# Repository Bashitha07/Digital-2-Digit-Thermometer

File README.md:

# 2-Digit Digital Thermometer

A low-cost, analog **2-digit digital thermometer** designed to measure temperatures from **0 °C to 99 °C**. This project was developed for the **IE2044 – System Modelling and Prototyping** module using an LM35 temperature sensor, a TC7107 ADC/display driver, and dual seven-segment displays.

## 📌 Project Overview

The thermometer converts the LM35 sensor output directly into a temperature reading without using a microcontroller or firmware. Since the LM35 produces **10 mV/°C**, the circuit is calibrated so that each degree Celsius corresponds to one displayed count.

The design combines:

- An **LM35 precision temperature sensor**
- A **TC7107 / ICL7107 analog-to-digital converter and display driver**
- Two **common-cathode seven-segment displays**
- A calibrated **100 mV reference voltage**
- Analog star-point grounding to reduce display jitter and noise
- Visual indication for temperature overflow and underflow conditions

## ✨ Key Features

- **Measurement range:** 0 °C to 99 ��C
- **Direct voltage scaling:** 10 mV from the LM35 represents 1 °C
- **Reference calibration:** 100 mV using a 1 kΩ trimmer potentiometer
- **No microcontroller required:** Fully analog measurement and display chain
- **Overflow indication:** Red LED for temperatures above 99 °C
- **Underflow indication:** Green LED for temperatures below 0 °C
- **Noise reduction:** Analog star-point grounding using `ADND*`
- **Dual-supply operation:** +5 V and −5 V rails
- **PCB design:** Single-layer routing with SMD 0805 components

## 🧠 Operating Principle

The LM35 generates an output voltage proportional to the measured temperature:

```text
VLM35 = 10 mV × Temperature (°C)
```

For example:

```text
25 °C → 250 mV
75 °C → 750 mV
```

The TC7107 measures this analog voltage and drives the two seven-segment displays. With the reference voltage calibrated to **100 mV**, the displayed value corresponds directly to the temperature in degrees Celsius.

## 🛠️ Component Summary

| Reference | Component | Package / Type | Purpose |
|:--:|---|---|---|
| U1 | TC7107 / ICL7107 | DIP-40 | Analog-to-digital conversion and display driving |
| U2 | LM35 | TO-92, through-hole | Precision Celsius temperature sensing |
| DIS1, DIS2 | Seven-segment displays | Common cathode | Tens and units temperature display |
| RV1 | Trimmer potentiometer, 1 kΩ | Through-hole | Reference voltage adjustment |
| R1–R6 | Resistors | SMD 0805 | Input conditioning, scaling, integration, oscillator, and LED current limiting |
| C1–C4 | Capacitors | SMD 0805 | Integrator, auto-zero, reference, and oscillator timing |

## 📁 Repository Contents

```text
Digital-2-Digit-Thermometer-/
├── Diagrams/               # System block diagrams and architecture diagrams
├── Report/                 # Final project report
├── Schematics/             # Proteus simulation files and EasyEDA PCB sources
├── SMP final project.pdf   # Official module project brief and specifications
└── README.md               # Project documentation
```

## 🧪 Simulation and PCB Implementation

### Phase I — Simulation

The circuit was tested in **Proteus Design Suite 8.06** across the complete 0 °C to 99 °C operating range. The simulation also validates:

- Normal temperature measurements
- Overflow conditions above 99 °C
- Underflow conditions below 0 °C
- Seven-segment display operation
- LED error indication
- Reference-voltage calibration

### Phase II — PCB Design

The PCB was developed using **EasyEDA Pro** with the following design requirements:

- Single-layer routing
- SMD 0805 resistor and capacitor footprints
- Analog star-point grounding
- Reduced digital switching noise
- Horizontally aligned seven-segment displays
- Layout suitable for practical assembly and testing

## 🔌 Power Requirements

The design uses a dual-supply configuration:

| Supply Rail | Main Purpose |
|---|---|
| `+5 V` | Logic, display-driving, and indicator circuitry |
| `−5 V` | Analog signal processing and internal integrator operation |

> **Safety note:** Verify the power-supply polarity and voltage levels before connecting the circuit. Incorrect supply connections may damage the TC7107, LM35, displays, or other components.

## 👥 Project Team

**Module:** IE2044 – System Modelling and Prototyping  
**Academic Year:** Year 2, Semester 2  
**Institution:** Sri Lanka Institute of Information Technology (SLIIT)  
**Group:** 05

| Student | Student ID |
|---|---|
| Sellapperuma B.A. | IT24103485 |
| Jayasinghe L.P. | IT24100888 |

## 📚 Technologies and Tools

- **Proteus Design Suite 8.06** — Circuit simulation
- **EasyEDA Pro** — Schematic capture and PCB design
- **LM35** — Analog temperature sensing
- **TC7107 / ICL7107** — ADC and seven-segment display driving

## 📄 License

This project was created for academic and educational purposes as part of the IE2044 module.

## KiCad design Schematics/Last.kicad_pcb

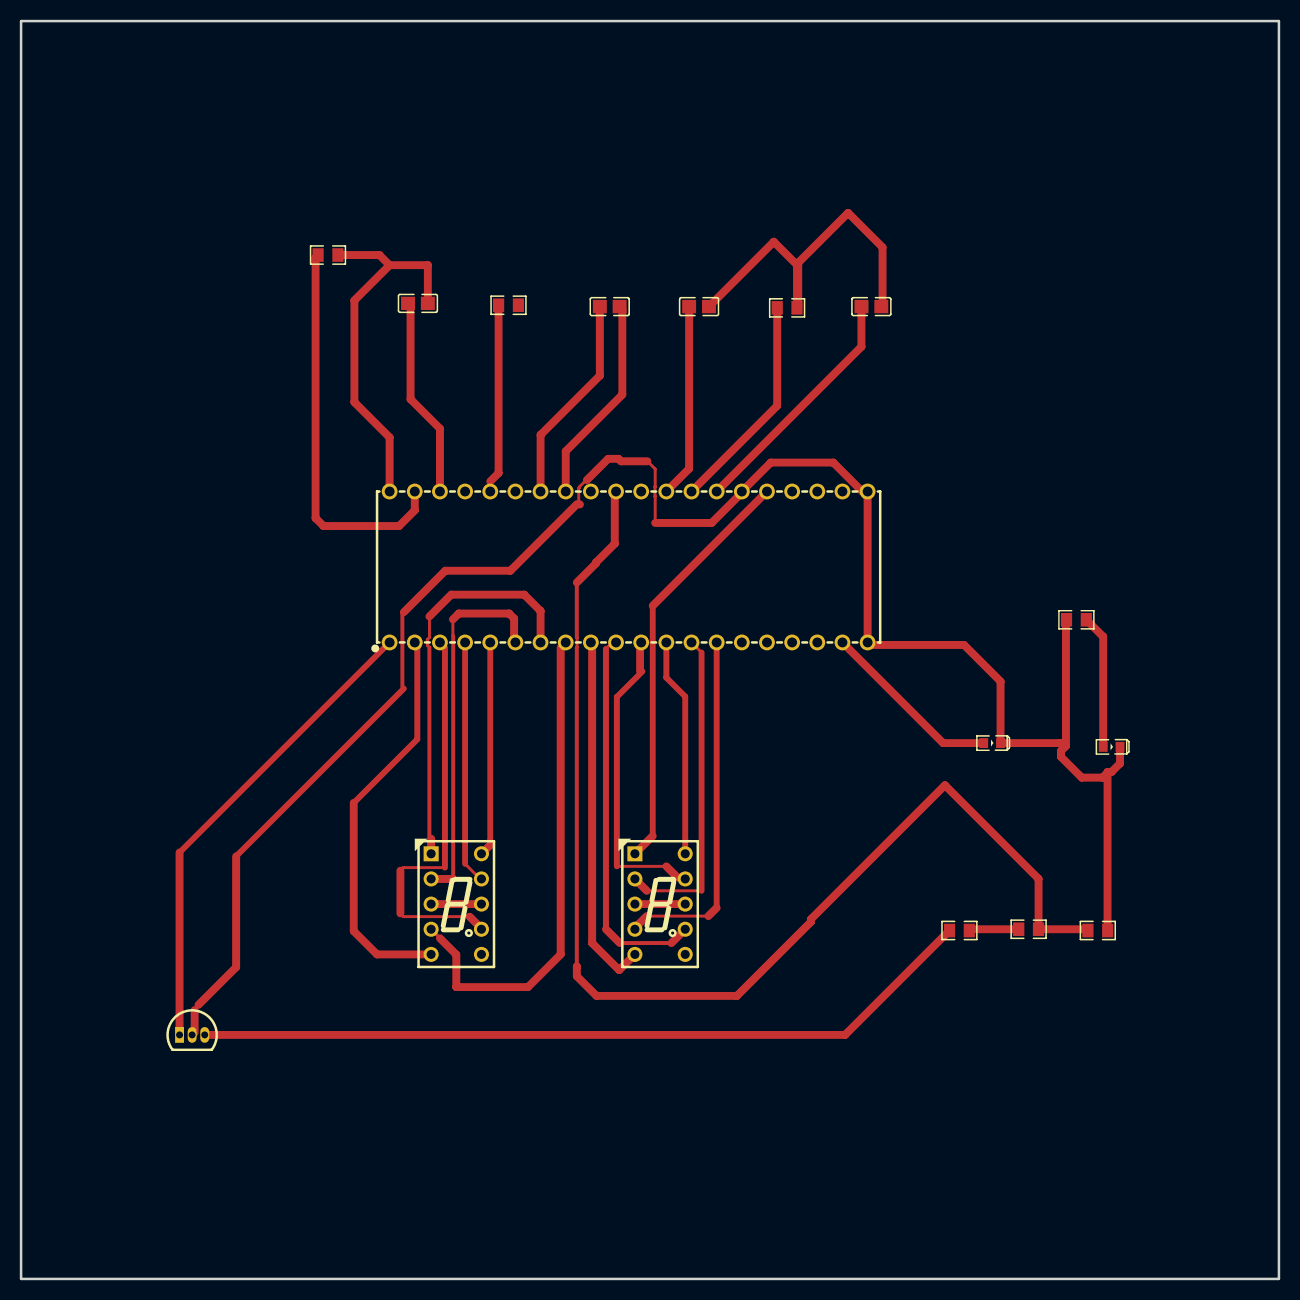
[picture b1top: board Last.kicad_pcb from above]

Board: 2 copper layers, 127.0 x 127.0 mm, 17 parts (0 on the bottom side), 33 nets.

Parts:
C2, C3, C4, C5: C0805
LED1, LED2: LED-SEG-TH_10P-L12.7-W7.6-P2.54-LS5.08-TL_LSHD-7501
LED3: LED0603_RED
LED4: LED0603_GREEN
R1, R2, R3, R4, R5, R6, R7: R0805
U1: DIP-40_L50.8-W15.3-P2.54-LS15.24-BL
U2: TO-92-3_L4.9-W3.7-P1.27-L_BT169D

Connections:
$1N1: C4.2, R4.2, U1.40
$1N2: C4.1, U1.38
$1N3: R4.1, U1.39
$1N6: R1.1, R5.2
$1N7: R5.1, U2.2
$1N9: C2.2, C3.2, R2.2
$1N10: C2.1, U1.29
$1N11: R2.1, U1.28
$1N12: C3.1, U1.27
$1N13: C5.1, U1.34
$1N14: C5.2, U1.33
$1N16: LED4.1, R6.2
$1N18: LED3.1, U1.19
$1N21: R7.1, U1.36
$1N24: LED2.10, U1.5
$1N25: LED2.9, U1.4
$1N26: LED2.7, U1.3
$1N27: LED2.4, U1.8
$1N28: LED2.5, U1.2
$1N29: LED2.2, U1.6
$1N30: LED1.1, U1.25
$1N31: LED2.1, U1.7
$1N33: LED1.9, U1.11
$1N34: LED1.7, U1.10
$1N35: LED1.10, U1.12
$1N36: LED1.2, U1.13
$1N37: LED1.4, U1.14
$1N38: LED1.5, U1.9
GND2: LED3.2, LED4.2, R3.2, R6.1, U1.20, U1.21, U1.26, U2.3
VCC: U1.1, U2.1
VCC2: LED2.3, LED2.8
VCC3: LED1.3, LED1.8
VOLPROBE1: R1.2, R3.1, U1.31
